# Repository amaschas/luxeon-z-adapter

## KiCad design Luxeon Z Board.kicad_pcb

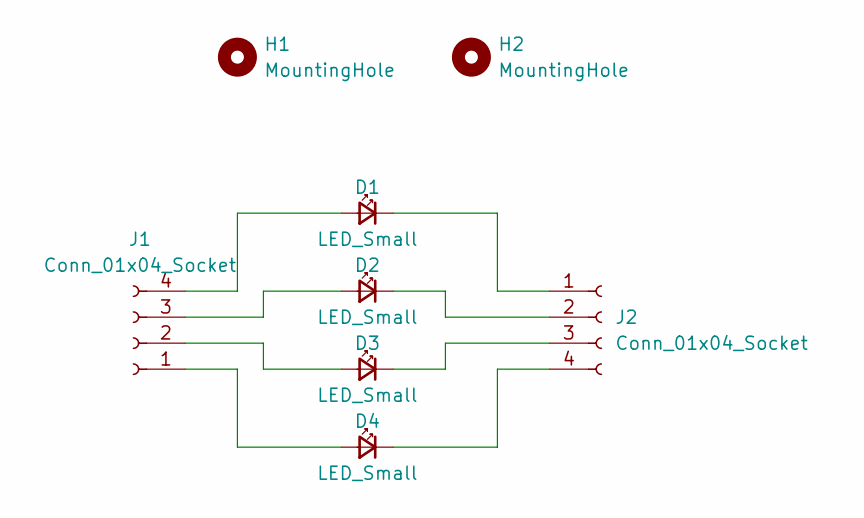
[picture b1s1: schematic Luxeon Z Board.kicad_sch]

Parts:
D1, D2, D3, D4: LED_Small; Luxeon Z Color
H1, H2: MountingHole; MountingHole_4.3mm_M4
J1, J2: Conn_01x04_Socket; S4B-XH-SM4-TB

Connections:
unnamed: D1.2 (A), J1.3
unnamed: D1.1 (K), J2.2
unnamed: D2.2 (A), J1.4
unnamed: D2.1 (K), J2.1
unnamed: D3.2 (A), J1.2
unnamed: D3.1 (K), J2.3
unnamed: D4.2 (A), J1.1
unnamed: D4.1 (K), J2.4

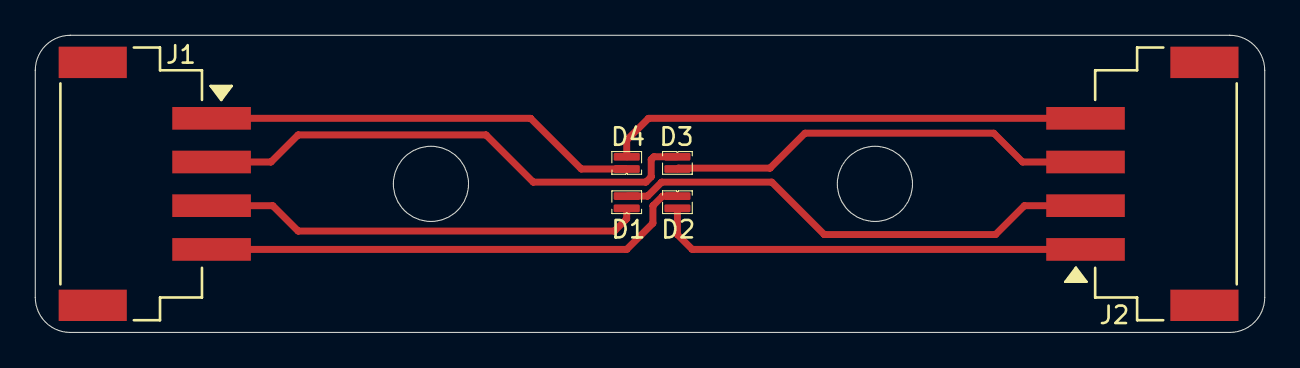
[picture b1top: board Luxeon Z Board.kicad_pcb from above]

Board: 4 copper layers, 70.3 x 17.0 mm, 8 parts (0 on the bottom side), 8 nets.

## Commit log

2023-12-18 initializing repo
